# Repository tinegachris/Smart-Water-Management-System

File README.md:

# Smart-Water-Management-System

>Final Project 2021

## Abstract

The Smart Water Management System project aggregates three meters to enable remote and automatic real-time measurement of water consumption. Based on actionable decisions such as water leakage and consumption metrics, water supply through the pipes is controlled using solenoid valves. The consumer and the supplier can monitor, visualize consumption metrics and control the system through the designed android interface.

## Acknowledgement

I acknowledge the efforts of my project partner Mr [Thoenes Kimani](https://www.linkedin.com/in/thoenes-kimani-607682186/) and my project supervisor Mr [Samson N. Njoroge](https://www.linkedin.com/in/samson-n-njoroge-23a77817/?originalSubdomain=ke), for ensuring this project was successful. Many thanks to all our friends and family for the encouragement and support throughout the period.

## System Overview

The system consists of four functional modules, namely: the physical device, the gateway through which the device communicates with the backend service, the backend that allows storage of data, analysis, data access and notifications and the interface that allows visualization and control.

>

## Concept Diagram

The Concept Diagram provides an overview of the system's architecture, illustrating the main components and their relationships. It helps in understanding the high-level design and the flow of data between different parts of the system.

The system consists of three meters: the supply meter, 1 and customer meters, 2 and 3 as shown below.

>

You can view and edit the detailed Concept Diagram using the provided `.vsdx` file using Microsoft Visio app:

- [Concept Diagram.vsdx](https://github.com/tinegachris/Smart-Water-Management-System/blob/e62496e4574b8286091f124c95a754fc847280cd/Concept%20Diagram.vsdx)

## System Flow Chart

The System Flow Chart illustrates the step-by-step flow of operations within the Smart Water Management System. It shows the sequence of actions and decision points, making it easier to understand the system's logic and workflow.

>

You can view and edit the detailed System Flow Chart using the provided `.vsdx` file using Microsoft Visio app:

- [System Flow Chart.vsdx](https://github.com/tinegachris/Smart-Water-Management-System/blob/e62496e4574b8286091f124c95a754fc847280cd/System%20flow%20chart.vsdx)

## System Components

1. **Three NodeMCU ESP8266** - [Component Overview](https://components101.com/development-boards/nodemcu-esp8266-pinout-features-and-datasheet)
2. **Three YF-S201 Hall Effect Water Flow Sensor** - [Component Overview](https://components101.com/sensors/yf-s201-water-flow-measurement-sensor)
3. **Three 2 Way, 2 Position, 12 VDC, 0.5 Inch, NC Solenoid Valve** - [Particular](https://www.twinschip.com/Solenoid_Valve_DC12V_0.5inch_Normally_Closed) ~~Not an affiliate link~~
4. **Three SRD-05VDC-SL-C Relay Module** - [Component Overview](https://elearn.ellak.gr/mod/book/view.php?id=4568&chapterid=2440)
5. **Three Power Supply Adapter 12V 2A**
6. **0.5 Inch Clear hose pipe - approx. 3 meters**
7. **One 0.5 Inch Plastic tap**
8. **Appropriate pipe fittings**

## Schematic Diagram

The schematic diagram of the system was designed using Autodesk's Eagle EDA software illustrating how the various components are interconnected.

Custom libraries for the solenoid valve and the water flow sensor were created.

>

## PCB Design

Design of the board from the schematic diagram was done as shown below.

>

## Firmware Walkthrough

- **Libraries**

The ESP8266WiFi, ESP8266WebServer, ESP8266mDNS and the ThingSpeak libraries were included.

```
#include <ESP8266WiFi.h> // ESP8266WiFi library
#include<ESP8266WebServer.h> // WebServer library
#include <ESP8266mDNS.h> // mDNS library
#include<ThingSpeak.h> // ThingSpeak library
```

- **Variables and Constants**

The variables and constants were defined as follows.

```
const int measuringInterval = 0.1 * 1000; // measure flow every 1 second
const int postingInterval = 15 * 1000; // post data every 15 seconds

long currentMillis = 0, previousMillis = 0;

float calibrationFactor_1 = 0.1;
volatile byte pulseCount_1;
byte pulse1Sec_1 = 0;
float flowRate_1;
unsigned long flowMilliLitres_1, totalMilliLitres_1;
float flowLitres_1, totalLitres_1;

// Control solenoid valve
const int controlChannelID = XXXXXXX; //ThingSpeak channel used for control
unsigned int valve1 = 4;
```

- **Wi-Fi Settings**

The SSID and password are set to allow the NodeMCU to connect to a network

```
const char* ssid = "mySSID"; // wireless network name (SSID)
const char* password = "myPassword"; // Wi-Fi network password
```

- **ThingSpeak Settings**

ThingSpeak credentials and API key are set to allow sending data to specific channel.

```
// ThingSpeak Settings
const int channelID = YYYYYYY;
String writeAPIKey = "XXXXXXXXXXXXXXXX";
const char* server = "api.thingspeak.com";
```

- **Serial Communication**

The baud rate for serial communication  set was to 115200.

```
  void setup() {
  Serial.begin(115200); // Start the Serial communication
  delay(100);
```

- **Define pins and initialize variables**

```
  pulseCount_1 = 0;
  flowRate_1 = 0.0;
  flowMilliLitres_1 = 0;
  totalMilliLitres_1 = 0;
  
  pinMode(flowSensor_1, INPUT_PULLUP);  
  pinMode(relayValve_1, OUTPUT);
  digitalWrite(relayValve_1, 0);
```

- **Connect to Wi-Fi network**

The NodeMCU waits until it is connected to a network then sends the IP address, Netmask and Gateway to the serial monitor.

```
WiFi.begin(ssid, password);             // Connect to the WiFi network
  Serial.print("Connecting to ");
  Serial.print(ssid); Serial.println("...");

  while (WiFi.status() != WL_CONNECTED) { // Wait for the Wi-Fi to connect
    delay(500);
  }
  
  Serial.println("WiFi connected!"); 
  // Send the IP address of the ESP8266 to serial monitor 
  Serial.print("IP address:\t");
  Serial.println(WiFi.localIP()); 
  // Send the Netmask of the ESP8266        
  Serial.print("Netmask:\t");
  Serial.println(WiFi.subnetMask());  
  // Send the Gateway of the ESP8266
  Serial.print("Gateway:\t");
  Serial.println(WiFi.gatewayIP());
```

- **Measure Wi-Fi Strength**

The Wi-Fi strength is measured and sent to the serial monitor.

```
// Measure Signal Strength (RSSI) of Wi-Fi connection
long rssi = WiFi.RSSI();
String strgth = String(rssi);
Serial.println("signal strength: " + strgth + "dB\n");
```

- **HTTP server**

The HTTP server that listens for HTTP request on port 80. The mDNS responder is also started to resolve IP address to a local domain name.

```
  // Create a webserver object that listens for HTTP request on port 80
  ESP8266WebServer server(80);

  // Start the mDNS responder for esp8266.local
  if (MDNS.begin("esp8266")) {              
  Serial.println("mDNS responder started");
  } else {
    Serial.println("Error setting up MDNS responder!");
  }

  server.begin(); // Actually start the server
  Serial.println("HTTP server started");
  
  //create interrupt and call a function when change is detected
  attachInterrupt(digitalPinToInterrupt(flowSensor_1), pulseCounter_1, FALLING);

  ThingSpeak.begin(client);
```

- **FLow Sensor Interrrupt**

An interrupt and a call function is created to detect water flow when the falling edge of the pulse is received.

```
//create interrupt and call a function when change is detected
  attachInterrupt(digitalPinToInterrupt(flowSensor_1), pulseCounter_1, FALLING);
```

The pulse count is incremented for every pulse that is detected.

```
void IRAM_ATTR pulseCounter_1(){
  pulseCount_1++;
}
```

- **Flowrate and Volume Calculation**

The flowrate and volume through the meter is measured and calculated after every measuring interval. The total volume is the cumulative volume in the entire measuring time.

```
currentMillis = millis();
  // calculate after every measuring interval
  if (currentMillis - previousMillis > measuringInterval) {
    
    pulse1Sec_1 = pulseCount_1;
    pulseCount_1 = 0;

     //calculate flow rate in litres per min
    flowRate_1 = ((1000.0 / (millis() - previousMillis)) * pulse1Sec_1) / calibrationFactor_1;
    previousMillis = millis();

    //flowrate in millilitres per second
    flowMilliLitres_1 = (flowRate_1 / 60) * 1000;

    //flowrate in litres per second
    flowLitres_1 = (flowRate_1 / 60);

    //add volume flowed in this second to cumulative totals
    totalMilliLitres_1 += flowMilliLitres_1;
    totalLitres_1 += flowLitres_1;

    // Print the flow rate 1 for this second in litres / minute
    Serial.print("Flow rate 1: ");
    Serial.print(flowMilliLitres_1);
    Serial.print(" mL/s\t");
    
    // Print the cumulative total of litres flowed through meter 1 since starting
    Serial.print("Volume through meter 1: ");
    Serial.print(totalMilliLitres_1);
    Serial.print(" mL\n");
//    Serial.println("Volume through meter 1: "); //Uncomment for volume in litres
//    Serial.print(totalLitres_1);
//    Serial.println(" L\n");
```

- **API request body**

The body of API request with consumption data are constructed waiting to be posted to ThingSpeak on specific fields.

```
      // Construct API request body
      String body = "field1=";
      body += String(float(flowRate_1));
      body += "&field2=";
      body += String(totalMilliLitres_1);
      body += "&field3=";
      body += strgth;
      body += "\r\n\r\n";
```

- **Post to ThingSpeak**

The API requests bodies are written to the corresponding fields on ThingSpeak on the specified channel. Feedback on if the data was sent successfully is sent to the serial monitor.

```
      client.print("POST /update HTTP/1.1\n");
      client.print("Host: api.thingspeak.com\n");
      client.print("Connection: close\n");
      client.print("X-THINGSPEAKAPIKEY: " + writeAPIKey + "\n");
      client.print("Content-Type: application/x-www-form-urlencoded\n");
      client.print("Content-Length: ");
      client.print(body.length());
      client.print("\n\n");
      client.print(body);
      client.print("\n\n");
      Serial.println("data sent\n");
```

- **Solenoid Valve Status**

The status of solenoid valve i.e. if it is open or closed is checked from the control feed and status sent to the serial monitor.

```
      //get the last data of the fields
      int valve_1 = ThingSpeak.readFloatField(controlChannelID, valve1);
    
      if(valve_1 == 1){
        digitalWrite(relayValve_1, 1); // Open solenoid valve
        Serial.println("Solenoid valve is Closed!\n");
        }
      else if(valve_1 == 0){
        digitalWrite(relayValve_1, 0); //Close solenoid valve
        Serial.println("Solenoid valve is Open!\n");
        }
```

- **Wait and Post Again**

```
    client.stop();
    
    Serial.print("Waiting ");
    Serial.print(postingInterval/1000);
    Serial.print(" seconds to post again...\n");
    
    // wait and then post again
    delay(postingInterval);
```

## **ThingSpeak Apps**

- ### MATLAB Analysis

The MATLAB Analysis app was used to perform loss analysis as shown below.

>

- ### ThingTweet

The ThingTweet app is utilized to send alert consumers via a tweet that the supply meter valve is closed due to any predetermined circumstance is encountered. The tweet is configured as below.

>

- ### TimeControl

TimeControl app feature was used in loss analysis calculation where losses due to leakages was calculated every 5 minutes as shown in the configuration below.

>

- ### React

React app feature was also used in the project in several instances such as sending email, SMS and VoIP calls when a certain condition is encountered.

>

## App Installation and Usage Instructions

### Installing the Smart Water App

#### For Developers (Using .aia File)

1. **Download the .aia File:**
   - Download the [Smart_Water_App.aia](https://github.com/tinegachris/Smart-Water-Management-System/blob/main/Smart_Water_App.aia) file from the repository.

2. **Open MIT App Inventor:**
   - Go to [MIT App Inventor](https://appinventor.mit.edu/).

3. **Import the .aia File:**
   - Click on "Projects" in the top menu.
   - Select "Import project (.aia) from my computer".
   - Choose the downloaded .aia file and click "OK".

4. **Build the App:**
   - After importing, you can modify the app as needed.
   - To build the app, click on "Build" in the top menu and select "App (provide QR code for .apk)" or "App (save .apk to my computer)".

#### For Users (Using .apk File)

1. **Download the .apk File:**
   - Download the [Smart_Water_App.apk](https://github.com/tinegachris/Smart-Water-Management-System/blob/main/Smart_Water_App.apk) file from the repository.

2. **Enable Unknown Sources:**
   - On your Android device, go to "Settings".
   - Navigate to "Security" or "Applications" (depending on your device).
   - Enable "Unknown sources" to allow installation of apps from sources other than the Google Play Store.

3. **Install the App:**
   - Open the downloaded .apk file on your Android device.
   - Follow the on-screen instructions to install the app.

### Using the Smart Water App

1. **Open the App:**
   - Locate the Smart Water App icon on your device and open it.

2. **Login:**
   - Enter your credentials to log in to the app.

3. **Monitor and Control:**
   - Use the app interface to monitor water consumption metrics.
   - Control the water supply through the solenoid valves remotely.

4. **Alerts and Notifications:**
   - Receive alerts and notifications for water leakage and other actionable events.

## **Interface**

The android app used as interface to visualize consumption data and control water supply remotely was designed using [MIT App Inventor](https://appinventor.mit.edu/).

The [.aia source code](https://github.com/tinegachris/Smart-Water-Management-System/blob/main/Smart_Water_App.aia) file is attached.

Download and install the [android app](https://github.com/tinegachris/Smart-Water-Management-System/blob/main/Smart_Water_App.app)

>                    

## Results

The system utilized IoT solutions to enable remote and automatic and real-time measurement of water consumption data which is transmitted to a remote server for manipulation and analysis.

>

The data was then displayed on an interface where consumption metrics, over a period, was be viewed.

>                         

The system developed aggregated multiple meters and performed loss analysis hence detecting water leakage. SMS, call, email and [tweet](https://twitter.com/smart_water_app/status/1463631460607344641?t=qJkpamW6DDiH7IFD41dn9Q&s=19) alerts allowed appropriate actions to be taken.

>                

Users could control water supply remotely from the interface based on actionable decisions.

> 
> 
> 

## Conclusion

The Smart Water Management System solution would be revolutionary for home and industrial systems by enabling remote and automatic measurement of consumption data, convenient monitoring and control of water systems and reducing water leakage - reducing non-revenue water hence saving on cost.

##

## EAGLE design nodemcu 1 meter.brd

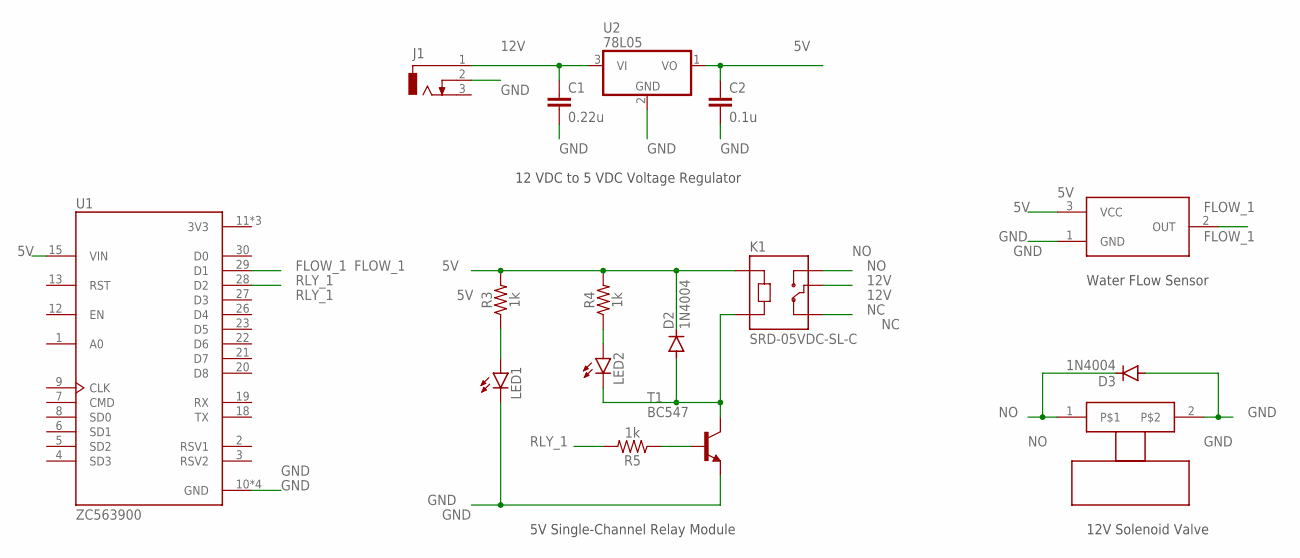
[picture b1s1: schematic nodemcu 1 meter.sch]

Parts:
C1: 0.22u; C025-025X050
C2: 0.1u; C025-025X050
D2, D3: 1N4004; DO41-10
FLOWSENSOR1: FLOWSENSOR
J1: DCJ0303
K1: SRD-05VDC-SL-C; RELAY_SRD-05VDC-SL-C
LED1, LED2: LED3MM
R3, R4, R5: 1k; AXIAL-0.3
T1: BC547; TO92
U1: ZC563900; MODULE_ZC563900
U2: 78L05; TO92
VALVE1: SOLENOID-VALVESOLENOID-CONNECTOR; 332-02

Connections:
3V3: U1.11 (3V3), U1.16 (3V3), U1.25 (3V3)
5V: C2.2, D2.C, FLOWSENSOR1.3 (VCC), K1.A1, R3.P$2 (2), R4.P$2 (2), U1.15 (VIN), U2.1 (VO)
12V: C1.2, J1.1, K1.COM, U2.3 (VI)
FLOW_1: FLOWSENSOR1.2 (OUT), U1.29 (D1)
GND: C1.1, C2.1, D3.A, FLOWSENSOR1.1 (GND), J1.2, LED1.K (C), T1.1 (E), U1.10 (GND), U1.14 (GND), U1.17 (GND), U1.24 (GND), U2.2 (GND), VALVE1.2
unnamed: R5.P$1 (1), T1.2 (B)
unnamed: D2.A, K1.A2, LED2.K (C), T1.3 (C)
unnamed: LED2.A, R4.P$1 (1)
unnamed: LED1.A, R3.P$1 (1)
NC: K1.NC
NO: D3.C, K1.NO, VALVE1.1
RLY_1: R5.P$2 (2), U1.28 (D2)

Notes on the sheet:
5V Single-Channel Relay Module
Water FLow Sensor
12V Solenoid Valve
12 VDC to 5 VDC Voltage Regulator

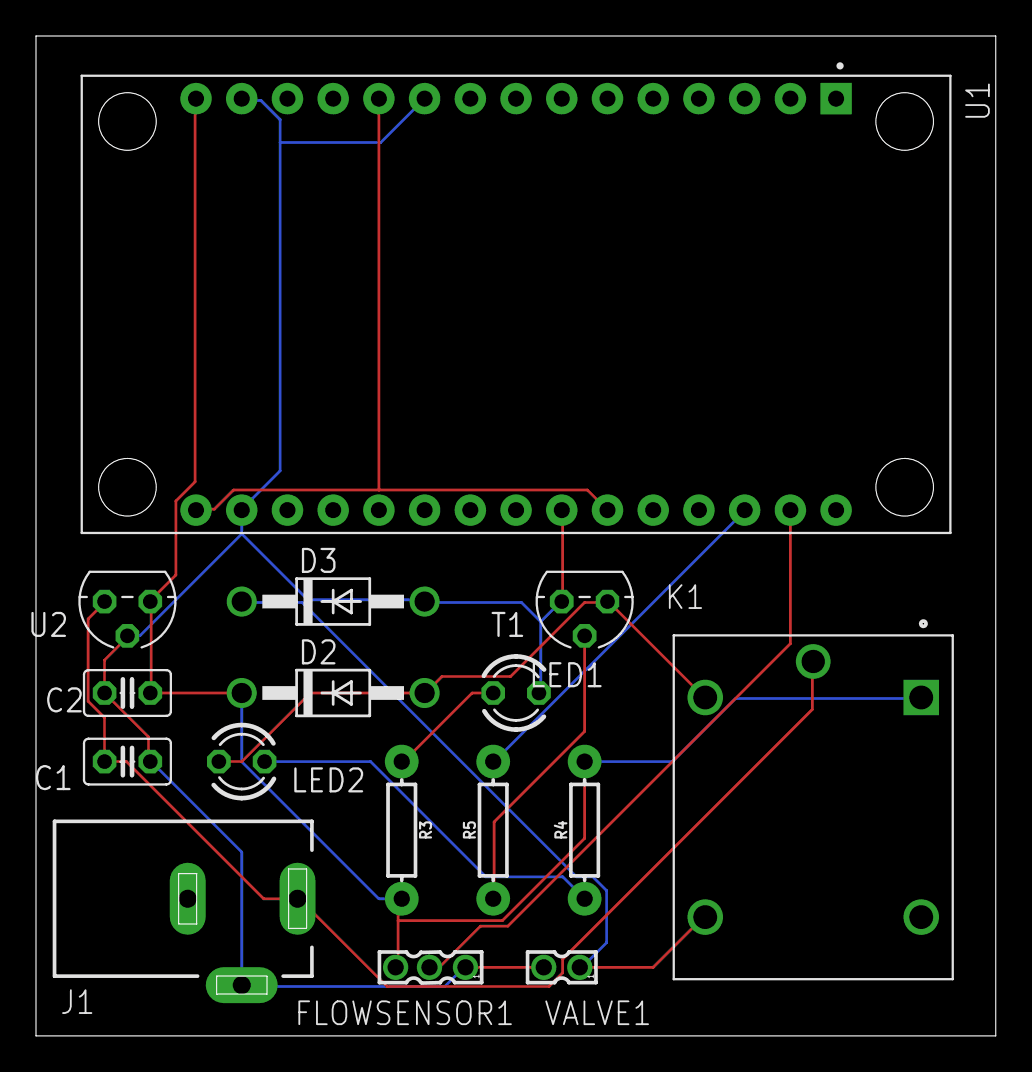
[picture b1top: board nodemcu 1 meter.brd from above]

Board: 2 copper layers, 53.3 x 55.5 mm, 16 parts (0 on the bottom side), 11 nets.

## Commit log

2021-11-28 Update readme 2
2021-11-28 Update Readme 3
2021-11-28 .aia source code file upload
2021-11-28 Update readme 4
2021-11-28 single meter firmware upload
2021-11-28 concept diagram & system flow chart upload
2021-11-28 eagle schematic file upload
2021-11-28 cover photo
2021-11-28 update readme 5
2021-11-28 android app
2021-11-29 header
2021-12-08 Board design and eagle sch upload
2021-12-09 Eagle custom libraries upload
2022-08-20 Header init
2022-08-20 publish
2022-08-20 removed ignore post
2024-11-13 Update README.md to fix badge links and improve formatting
2024-11-13 Add installation and usage instructions for the Smart Water App in README.md
2024-11-13 Update README.md to enhance diagrams section with descriptions and links to .vsdx files
2024-11-13 Refactor single_meter_and_control.ino for improved readability and maintainability

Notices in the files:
parts and their libraries:
SparkFun-Resistors: Licensing: Creative Commons ShareAlike 4.0 International - https://creativecommons.org/licenses/by-sa/4.0
